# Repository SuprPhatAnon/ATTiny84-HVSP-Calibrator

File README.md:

# TinyCalibrator - OSC Calibrator and High-Voltage Fuse Resetter

based on https://github.com/wagiminator/ATtiny84-TinyCalibrator

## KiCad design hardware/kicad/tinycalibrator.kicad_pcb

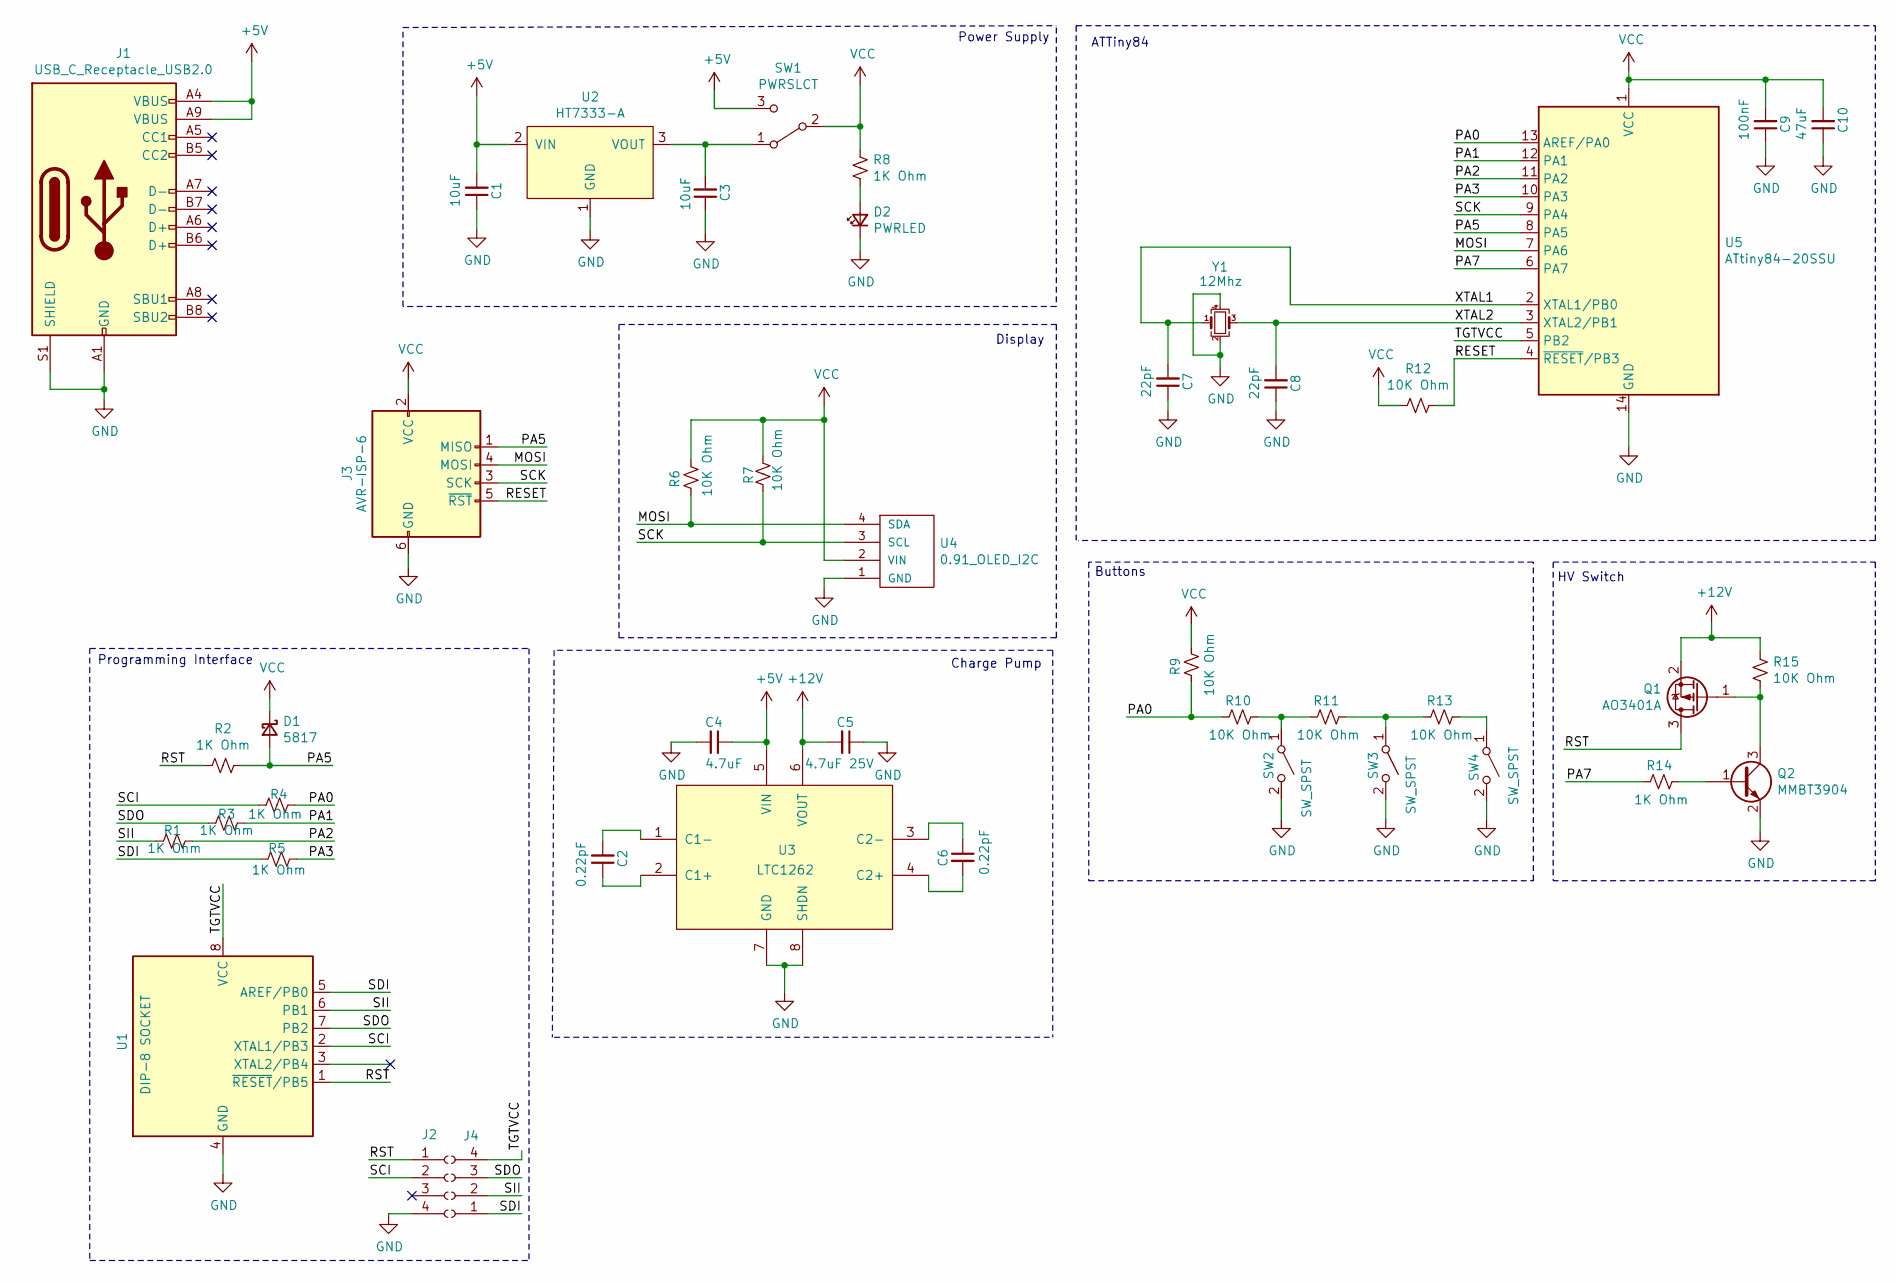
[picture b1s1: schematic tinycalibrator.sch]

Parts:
C1, C3: 10uF; C_0805_2012Metric_Pad1.15x1.40mm_HandSolder
C2, C6: 0.22pF; C_0805_2012Metric_Pad1.15x1.40mm_HandSolder
C4: 4.7uF; C_0805_2012Metric_Pad1.15x1.40mm_HandSolder
C5: 4.7uF 25V; C_0805_2012Metric_Pad1.15x1.40mm_HandSolder
C7, C8: 22pF; C_0805_2012Metric_Pad1.15x1.40mm_HandSolder
C9: 100nF; C_0805_2012Metric_Pad1.15x1.40mm_HandSolder
C10: 47uF; C_0805_2012Metric_Pad1.15x1.40mm_HandSolder
D1: 5817; D_DO-41_SOD81_P10.16mm_Horizontal
D2: PWRLED; LED_0805_2012Metric_Pad1.15x1.40mm_HandSolder
J1: USB_C_Receptacle_USB2.0; USB_C_Receptacle_GCT_USB4085
J2, J4: Conn_01x04_Female; PinSocket_1x04_P2.54mm_Vertical
J3: AVR-ISP-6; PinSocket_2x03_P2.54mm_Vertical
Q1: AO3401A; SOT-23
Q2: MMBT3904; SOT-23
R1, R2, R3, R4, R5, R8, R14: 1K Ohm; R_0805_2012Metric_Pad1.15x1.40mm_HandSolder
R6, R7, R9, R10, R11, R12, R13, R15: 10K Ohm; R_0805_2012Metric_Pad1.15x1.40mm_HandSolder
SW1: PWRSLCT; SWITCH_SPDT_PTH_11.6X4.0MM
SW2, SW3, SW4: SW_SPST; TACTILE_SWITCH_SMD_6.0X3.5MM
U1: DIP-8 SOCKET; DIP-8_W7.62mm_Socket
U2: HT7333-A; SOT-89-3_Handsoldering
U3: LTC1262; SO-8_3.9x4.9mm_P1.27mm
U4: 0.91_OLED_I2C; I2C_OLED_0.91
U5: ATtiny84-20SSU; SOIC-14_3.9x8.7mm_P1.27mm
Y1: 12Mhz; Crystal_SMD_5032-4Pin_5.0x3.2mm

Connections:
+5V: C1.2, C4.1, J1.A4 (VBUS), J1.A9 (VBUS), J1.B4 (VBUS), J1.B9 (VBUS), SW1.3 (C), U2.2 (VIN), U3.5 (VIN)
+12V: C5.2, Q1.2 (S), R15.2, U3.6 (VOUT)
/MOSI: J3.4 (MOSI), R6.2, U4.4 (SDA), U5.7 (PA6)
/PA0: R4.1, R9.2, R10.2, U5.13 (AREF/PA0)
/PA1: R3.1, U5.12 (PA1)
/PA2: R1.1, U5.11 (PA2)
/PA3: R5.1, U5.10 (PA3)
/PA5: D1.2 (A), J3.1 (MISO), R2.1, U5.8 (PA5)
/PA7: R14.2, U5.6 (PA7)
/RESET: J3.5 (~RST), R12.1, U5.4 (~RESET~/PB3)
/RST: J2.1, Q1.3 (D), R2.2, U1.1 (~RESET~/PB5)
/SCI: J2.2, R4.2, U1.2 (XTAL1/PB3)
/SCK: J3.3 (SCK), R7.2, U4.3 (SCL), U5.9 (PA4)
/SDI: J4.1, R5.2, U1.5 (AREF/PB0)
/SDO: J4.3, R3.2, U1.7 (PB2)
/SII: J4.2, R1.2, U1.6 (PB1)
/TGTVCC: J4.4, U1.8 (VCC), U5.5 (PB2)
/XTAL1: C7.2, U5.2 (XTAL1/PB0), Y1.1
/XTAL2: C8.2, U5.3 (XTAL2/PB1), Y1.3
GND: C1.1, C3.1, C4.2, C5.1, C7.1, C8.1, C9.1, C10.1, D2.1 (K), J1.A1 (GND), J1.A12 (GND), J1.B1 (GND), J1.B12 (GND), J1.S1 (SHIELD), J2.4, J3.6 (GND), Q2.2 (E), SW2.2 (B), SW3.2 (B), SW4.2 (B), U1.4 (GND), U2.1 (GND), U3.7 (GND), U3.8 (SHDN), U4.1 (GND), U5.14 (GND), Y1.2, Y1.4
unnamed: C2.1, U3.2 (C1+)
unnamed: C2.2, U3.1 (C1-)
unnamed: C3.2, SW1.1 (A), U2.3 (VOUT)
unnamed: C6.1, U3.3 (C2-)
unnamed: C6.2, U3.4 (C2+)
unnamed: D2.2 (A), R8.2
unnamed: Q1.1 (G), Q2.3 (C), R15.1
unnamed: Q2.1 (B), R14.1
unnamed: R10.1, R11.2, SW2.1 (A)
unnamed: R11.1, R13.2, SW3.1 (A)
unnamed: R13.1, SW4.1 (A)
VCC: C9.2, C10.2, D1.1 (K), J3.2 (VCC), R6.1, R7.1, R8.1, R9.1, R12.2, SW1.2 (B), U4.2 (VIN), U5.1 (VCC)

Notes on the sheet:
Charge Pump
Power Supply
ATTiny84
Display
HV Switch
Buttons
Programming Interface

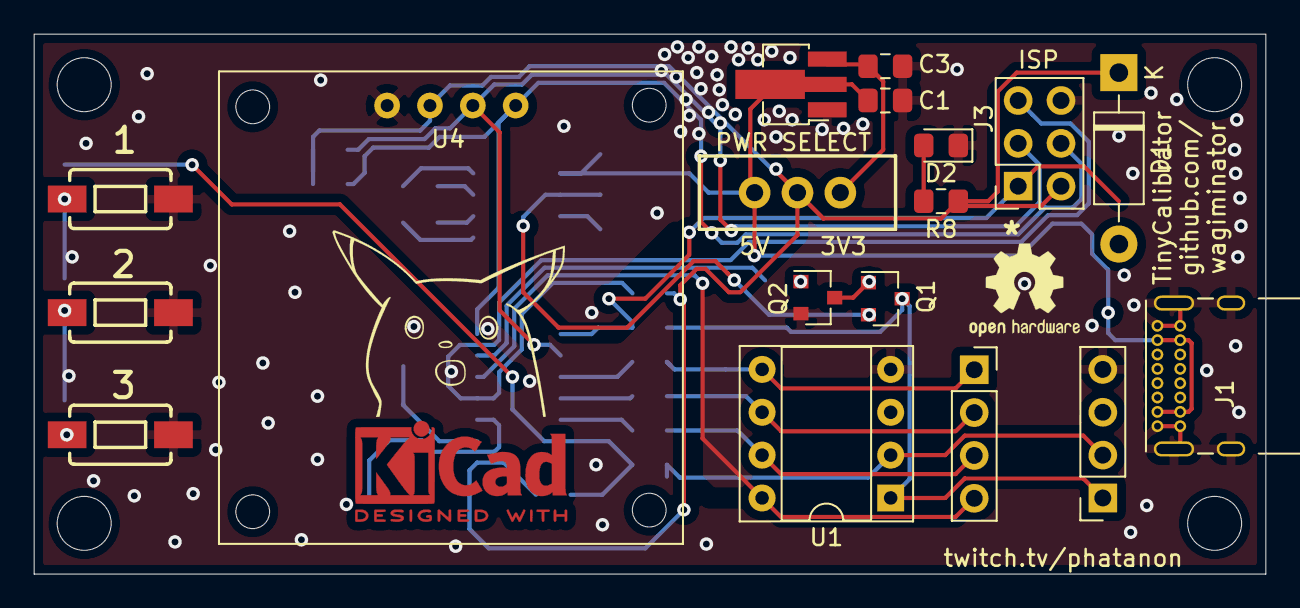
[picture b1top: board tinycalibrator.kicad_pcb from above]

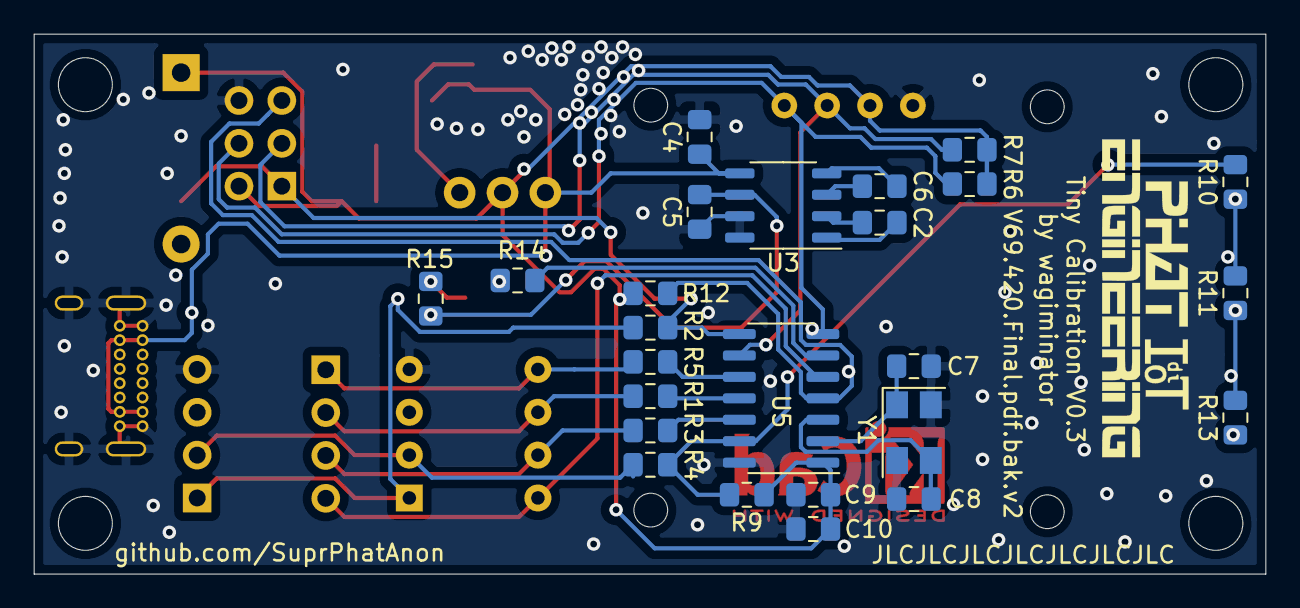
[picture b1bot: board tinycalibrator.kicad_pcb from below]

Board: 2 copper layers, 73.0 x 32.0 mm, 43 parts (25 on the bottom side), 32 nets.

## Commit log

2021-10-01 kicad commit
